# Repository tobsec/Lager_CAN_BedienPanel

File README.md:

Lager_CAN_BedienPanel
=====================

3teiliges Bedienpanel

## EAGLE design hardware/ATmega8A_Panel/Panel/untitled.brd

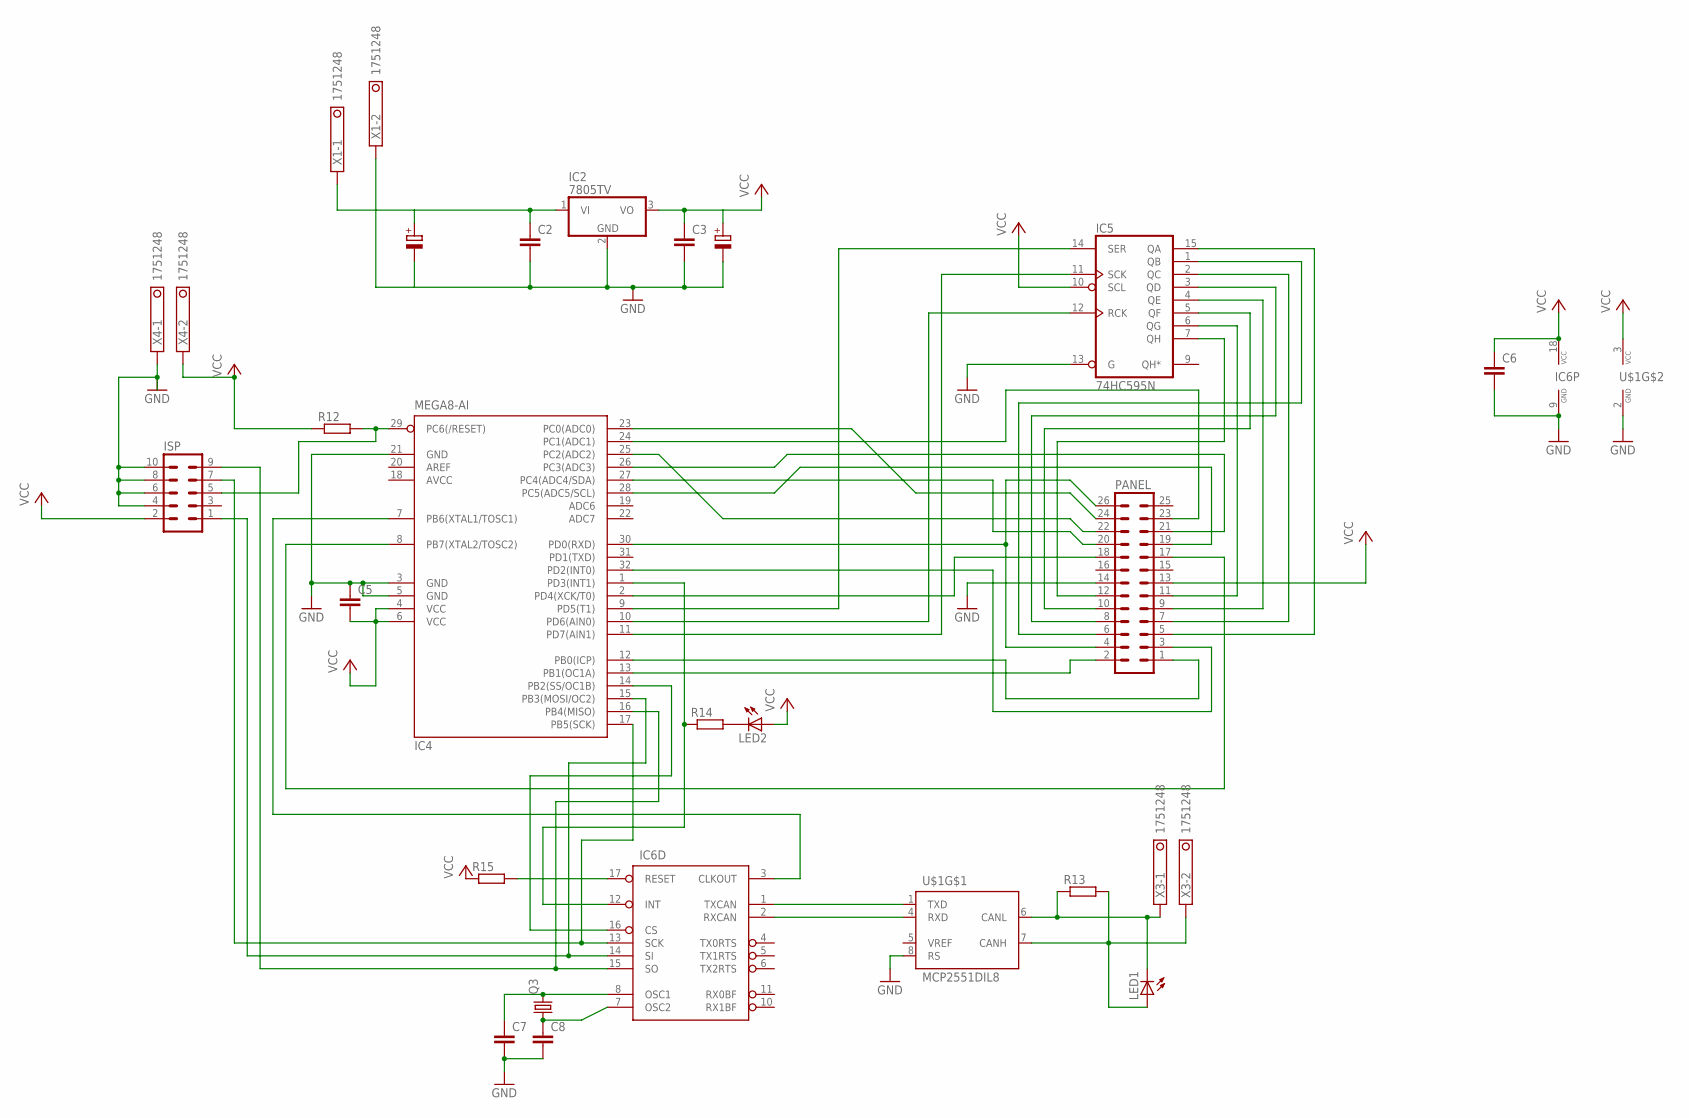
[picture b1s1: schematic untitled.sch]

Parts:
C2, C3, C5, C6, C7, C8: C2.5/2; C2.5-2
IC2: 7805TV; TO220V
IC4: MEGA8-AI; TQFP32-08
IC5: 74HC595N; DIL16
IC6: MCP2515P; DIL18
ISP: ML10
LED1, LED2: LED3MM
PANEL: ML26
Q3: CRYSTALHC49U-V; HC49U-V
R12, R13, R14, R15: R-EU_0207/10; 0207/10
U$1: MCP2551DIL8; DIL08
X1, X3, X4: 1751248

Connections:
AVCC: IC4.18 (AVCC)
GND: C2.2, C3.2, C5.1, C6.2, C7.2, C8.2, IC2.2 (GND), IC4.3 (GND), IC4.5 (GND), IC4.21 (GND), IC5.8 (GND), IC5.13 (G), IC6.9 (GND), ISP.4, ISP.6, ISP.8, ISP.10, PANEL.14, U$1.2 (GND), U$1.8 (RS), X1.2, X4.1
unnamed: LED1.K (C), R13.1, U$1.6 (CANL), X3.1
unnamed: IC4.29 (PC6(/RESET)), ISP.5, R12.2
unnamed: IC4.12 (PB0(ICP)), PANEL.1
unnamed: C2.1, IC2.1 (VI), X1.1
unnamed: IC4.13 (PB1(OC1A)), PANEL.2
unnamed: IC4.32 (PD2(INT0)), PANEL.3
unnamed: IC4.30 (PD0(RXD)), PANEL.4, PANEL.26
unnamed: IC5.15 (QA), PANEL.5
unnamed: IC5.1 (QB), PANEL.6
unnamed: IC5.2 (QC), PANEL.7
unnamed: IC5.3 (QD), PANEL.8
unnamed: IC5.4 (QE), PANEL.9
unnamed: IC5.5 (QF), PANEL.10
unnamed: IC5.6 (QG), PANEL.11
unnamed: IC5.7 (QH), PANEL.12
unnamed: LED1.A, R13.2, U$1.7 (CANH), X3.2
unnamed: LED2.K (C), R14.2
unnamed: IC4.7 (PB6(XTAL1/TOSC1)), IC6.3 (CLKOUT)
unnamed: IC4.8 (PB7(XTAL2/TOSC2)), PANEL.17
unnamed: IC4.1 (PD3(INT1)), IC6.12 (INT), R14.1
unnamed: IC6.1 (TXCAN), U$1.1 (TXD)
unnamed: IC6.2 (RXCAN), U$1.4 (RXD)
unnamed: C8.1, IC6.7 (OSC2), Q3.1
unnamed: C7.1, IC6.8 (OSC1), Q3.2
unnamed: IC4.23 (PC0(ADC0)), PANEL.24
unnamed: IC4.14 (PB2(SS/OC1B)), IC6.16 (CS)
unnamed: IC6.17 (RESET), R15.2
unnamed: IC4.16 (PB4(MISO)), IC6.15 (SO), ISP.9
unnamed: IC4.15 (PB3(MOSI/OC2)), IC6.14 (SI), ISP.1
unnamed: IC4.17 (PB5(SCK)), IC6.13 (SCK), ISP.7
unnamed: IC4.2 (PD4(XCK/T0)), PANEL.18
unnamed: IC4.28 (PC5(ADC5/SCL)), PANEL.19
unnamed: IC4.27 (PC4(ADC4/SDA)), PANEL.20
unnamed: IC4.26 (PC3(ADC3)), PANEL.21
unnamed: IC4.25 (PC2(ADC2)), PANEL.22
unnamed: IC4.24 (PC1(ADC1)), PANEL.23
unnamed: IC4.11 (PD7(AIN1)), IC5.11 (SCK)
unnamed: IC4.10 (PD6(AIN0)), IC5.12 (RCK)
unnamed: IC4.9 (PD5(T1)), IC5.14 (SER)
VCC: C3.1, C5.2, C6.1, IC2.3 (VO), IC4.4 (VCC), IC4.6 (VCC), IC5.10 (SCL), IC5.16 (VCC), IC6.18 (VCC), ISP.2, LED2.A, PANEL.13, R12.1, R15.1, U$1.3 (VCC), X4.2

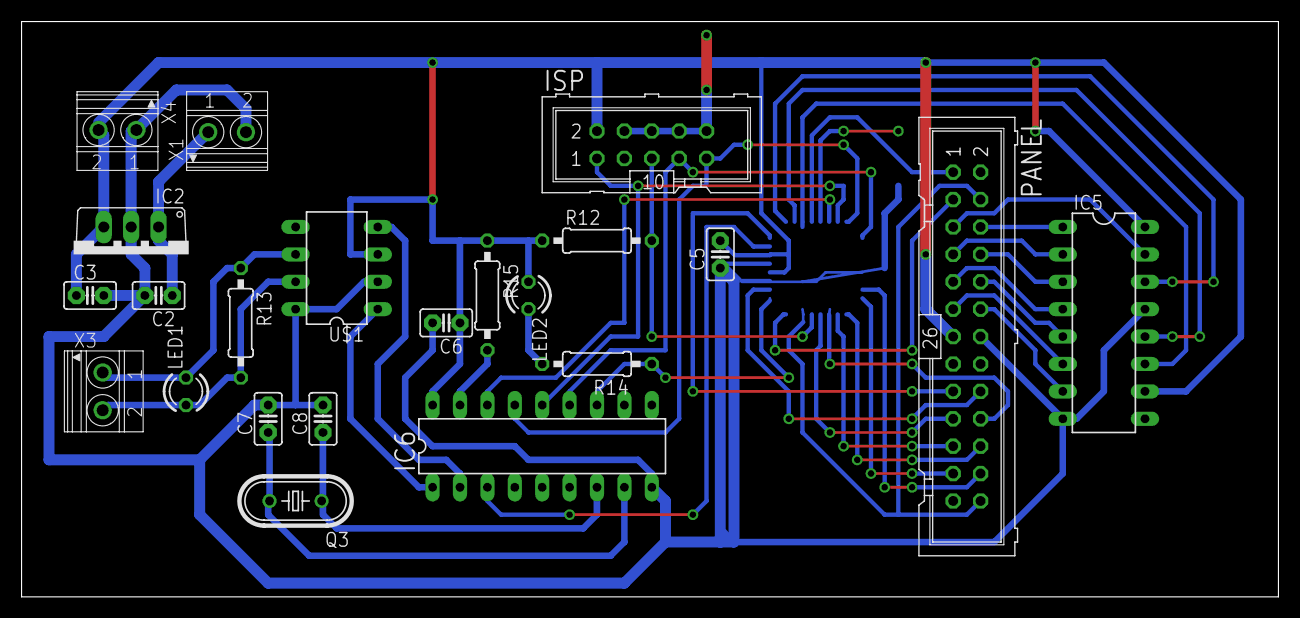
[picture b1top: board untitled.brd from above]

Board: 2 copper layers, 116.5 x 53.3 mm, 23 parts (1 on the bottom side), 41 nets.

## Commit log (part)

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2014-09-08 Commit des aktuellen Standes
2025-01-28 Convert to PlatformIO
2025-01-28 Add Eeagle PCB (old)
2025-01-28 Add KiCad PCB - as ordered
2025-01-28 add CAN requested reset for BL, LagerLight protocol V2, prepare CAN flashing
2025-01-28 Rework platformio for CAN flashing, add flashing batchs
2025-01-29 Refactored CAN functionality into a separate component and cleaned up indentation.
2025-02-15 Comments, adapt for the control panel PCB
